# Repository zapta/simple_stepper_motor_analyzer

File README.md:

# Simple Stepper Motor Analyzer

**NOTE:** (April 2023) A new design of a stepper motor analyzer is available at 
https://github.com/zapta/ble_stepper_motor_analyzer. The new design has similar capabilities to this one but uses a Bluetooth link and a Mac/Windows/Linux app to display the data in real time. It is also less expensive to produce and can be ordered fully assembled from JLCPCB SMD service. You can embed one or more of the new analyzers in your 3D printer and connect to them remotely whever you want.

**NOTE:** (Aug 2022) A variant of the Simple Stepper Motor Analyzer can be purchased in Japan at 
https://nyarurato.booth.pm/items/4025304 . International shipping is also available.

**IMPORTANT:** We are not associated with any seller nor do we have any experience with their products
which may or may not differ from the design here. The Simple Stepper Motor Analyzer is an *as-is*
open source design for educational purposes and people may chose to use it on their own risk.

&nbsp;

&nbsp;

&nbsp;

## Demonstration

Michael from the Teaching Tech youtube channel made [a great video explaining how stepper motors work](https://youtu.be/4iII25DGIdA) and used the Simple Stepper Motor Analyzer for some of the demonstrations. 

&nbsp;

## Highlights
* Low cost and minimalist DYI hardware design.
* Standalone. Doesn't require a computer to operate.
* Analyzes the stepper motor signals in the actual system (e.g. a 3D printer).
* Galvanically isolated current sensors. Does not interfere with the operating equipment, even when its turned off.
* Easy to connect using a pair 4 wire pass through connectors.
* Intuitive user interface with color display and a capacitive touch.
* Microstepping resolution of 1% of a full step.
* Provides momentary readings, signal patterns, and statistical measurements.
* Hardware and software are open sourced with a generous license.
* Based on free tools (Kicad, platformio, LVGL) and the Raspberry Pi Pico.
* Can be easily customized (new featured, cost reduction, data link to a computer, etc).
* Powered 5VDC, 200ma via a USB-C connector.

## Overview
Diagnosing the operation of stepper motor in 3D printers and CNC machines used to require stepper motor analyzers that costs thousands of dollar. Not anymore! The Simple Stepper Analyzer ('Analyzer' in short) brings these capabilities to every maker for a tiny fraction of the price and with a minimalist DIY electronic design that leaves the heavy lifting to the firmware.

The Analyzer is self contained, has two 4-wires pass-through connectors connecting the stepper motor, is powered from a common 5V charger with a micro USB cable, provides a simple to use graphical user interface with a 3.5" color touch screen, and provides a plethora of stepper motor measurements.

The Analyzer is provided to the community as a public domain reference design that can be built and used as is, or be customized with additional features or for a lower cost as desired. The hardware and firmware come with a liberal open source license (CC0) that allows commercial usages and doesn't require code source code sharing.

---
## Disclaimer
THE DESIGN IS PROVIDED "AS IS", WITHOUT WARRANTY OF ANY KIND, EXPRESS OR IMPLIED, INCLUDING BUT NOT LIMITED TO THE WARRANTIES OF MERCHANTABILITY, FITNESS FOR A PARTICULAR PURPOSE AND NONINFRINGEMENT. IN NO EVENT SHALL THE AUTHORS OR COPYRIGHT HOLDERS BE LIABLE FOR ANY CLAIM, DAMAGES OR OTHER LIABILITY, WHETHER IN AN ACTION OF CONTRACT, TORT OR OTHERWISE, ARISING FROM, OUT OF OR IN CONNECTION WITH THE DESIGN OR THE USE OR OTHER DEALINGS IN THE DESIGN.

---
## How does it work?
The principle of operation is very simple, and so is the hardware design. The stepper motor is connected via 4 wire pass-though connectors that allow the Analyzer to monitor the current through the stepper's coils. The Analyzer's user low impedance current sensors that are galvanically isolated such does not interfere with the operation of the 3D printer or other equipment it monitors. The Analyzer measures the coils currents 100k times a second and uses firmware that analyzes the data, extracts the desired measurements, and present them on the screen. For example, this is how an analysis of the distribution of distance by speed distribution looks like:

---
## Operation is simple and intuitive

1. Turn off power to the equipment (e.g. 3D printer).
2. Disconnect the 4 wires of the stepper motor and connect them through the Analyzer two pass through connectors.
3. Power the analyzer using a 5V charger and a micro USB cable.
4. Turn on the equipment and get the stepper going.
5. Use the Analyzer's screen to view the measurements you want.

**NOTE:** The two pass-through connectors of the Analyzer are symmetric and  each can act as an input or output. 

**CAUTION:** Always connect and disconnect stepper motors when their controller is not energized, to reduce the risk of damage to the controller due to high voltage spikes. The analyser itself is not subject to that risk since its uses galvanically isolated current sensors.

**NOTE:** The only requirement for proper wiring is that the two wires of one coil should go through pins pair 1,2 and the two wires of the other coil should go through pin pair 3,4. The Analyzer doesn't care about the +/- polarity of the wires in each pair, nor does it care which of the two pass-through connectors is on the controller side and which one is on the stepper side.

**TRIVIA:**: The pin-out and the connector type of the Analyzer follows the Duet3D conventions, except that is uses right angle connector to save space.

---
## The Home Page
The Home page is first page shown when the Analyzer is powered on. It provides summary information as well as access to the Settings page.

&nbsp;

#### Page Data

Field | Description
:------------ | :-------------
 COIL&nbsp;1 | Momentary coil 1 current in Amps.
 COIL&nbsp;2 | Momentary coil 2 current in Amps.
 ERRORS | The number of phase errors detected so far. Phase errors happens when the current patterns are so distorted that a forward/backward movement cannot be determined.
 POWER | Indicates if the stepper motor is currently energized. This is determined by the sum of currents in they two coils.
 IDLES | The number of times that stepper motor change status from energized to non energized.
 STEPS | The distance the stepper moved so far. Each full step forward increments this value by one and each full step backward decrements it by one. When the stepper motor is energized, the display also shows fractional steps in resolution of 1/100th of a full step.

HINT: The fractional step value cannot be reset because it is derived from the momentary currents in the two coils. Only the stepper motor driver can reset the fraction by positioning the stepper motor on an exact full step.

HINT: To swap forward/backward directions of the Analyzer use the Settings page. This does not affect the stepper motor itself.

&nbsp;
#### Page Actions

Action | Description
:------------: | :-------------
 | Clear all data.
 | Open the Settings page.

&nbsp;

---

## The Settings Page

This is a special page that is accessible from the Home page and allows to calibrate the Analyzer. The settings are stored in a non volatile memory and are preserved when the Analyzer is turned off.

&nbsp;
#### Page Data

Data | Description
:------------: | :-------------
COIL&nbsp;1 | The momentary current of stepper coil 1 in Amp units. Should be zero, or very close to zero, when the stepper motor is disconnected.
COIL&nbsp;2 | The momentary current of stepper coil 2 in Amp units. Should be zero, or very close to zero, when the stepper motor is disconnected.

&nbsp;
#### Page Actions

Action | Description
:------------: | :-------------
SET ZERO | Used to calibrate the zero reading of the current sensors. To do so, Disconnect the stepper motor and press this button.
REVERSE STEPS DIRECTION | Changes the forward/backward step directions of the Analyzer. Does not affect the stepper motor itself. Having the correct direction is important for measurements such as the Retraction analysis.
 | Press exist the Settings page.

&nbsp;

---

## The Speed Dial Page

This page measure the stepper speed in units of full steps per second. 

&nbsp;
#### Page Data

Data | Description
:------------ | :-------------
Speed&nbsp;Dial | The speed dial shows the momentary stepper speed in full steps per second units. Forward speed is on the right side and backward speed is on the left.
Speed&nbsp;Value | This field shows the speed in a numeric form. IT is updated less frequently than the dial to allow easy reading.

&nbsp;
**HINT:** The Settings page allows to swap the forward/backward directions.

&nbsp;
#### Page Actions

Action | Description
:------------: | :-------------
 | Clears all data.
Tap the dial |Toggles the dial's speed range.

&nbsp;

---

## The Distance Graph Page

This page shows scrolling graph with the total number of full steps vs. time.

&nbsp;

#### Page Data

Data | Description
:------------ | :-------------
Distance&nbsp;Graph | This graph shows how the distance, in units of full steps, changes over time.
Distance&nbsp;value | The numeric value of the distance in full steps.  This fields is identical to the STEPS field in the Home page.

&nbsp;

#### Page Actions

Action | Description
:------------: | :-------------
 | Clears all data.
Tap the graph | Toggles the range of the vertical axis.

&nbsp;

---

#### The Retraction Graph Page

This page is useful to analyze the retraction in of 3D printer extruder.

&nbsp;
**TRIVIA:** The graph above was taken while testing a direct extruder printer with [Thing #909901](https://www.thingiverse.com/thing:909901).
&nbsp;
#### Page Data

Data | Description
:------------ | :-------------
Retraction&nbsp;Graph | This graphs tracks the retraction of 3D extruder full step units.  Retraction is defined as the filament length that was inside the extruder and is now retracted outside of the extruder. 
Retraction value |  This field shows the current retraction level in a numeric form.

&nbsp;
#### Page Actions

Action | Description
:------------: | :-------------
 | Clear all data.
Tap the graph | Changes the range of the vertical axis.

&nbsp;

---

## The Time by Speed Page

This page shows an histogram with the distributing of time by stepper speed. That is how much time was spent in each speed range. The values are normalized such that the longest bar is always at 100%.

&nbsp;
#### Page Data

Data | Description
:------------ | :-------------
Time&nbsp;Histogram | The horizontal axis indicates speed in full steps per second units. The height of each bar indicate the time of all steps in that speed range, with the length of the longest bar normalized to 100%.

&nbsp;
#### Page Actions

Action | Description
:------------: | :-------------
 | Clear all data.

&nbsp;

---

## The Distance by Speed Page

This page shows an histogram with the the distribution of distance by stepper speed.

&nbsp;
#### Page Data

Data | Description
:------------ | :-------------
Distance&nbsp;Histogram |  The horizontal axis indicates speed in full steps per second units. The height of each bar indicate the distance or number of steps in that speed range, with the length of the longest bar normalized to 100%.

&nbsp;
#### Page Actions

Action | Description
:------------: | :-------------
 | Clear all data.

&nbsp;

---

## The Current by Speed Page

This page measures the ability of the stepper motor's controller to maintain peak current at high speeds.

The screenshot below shows a healthy system where the peak current is virtually flat across the speed range.

The screenshot below shows a system that is not capable to maintain peak current and starves the stepper motor at high speeds, resulting in poor torque and possible skipped steps.

&nbsp;
#### Page Data

Data | Description
:------------ | :-------------
Peak&nbsp;Current&nbsp;Histogram | The horizontal axis indicates speed in full steps per second units. The height of each bar indicates the average peak current in Amps of  steps that speed range. 

&nbsp;
#### Page Actions

Action | Description
:------------: | :-------------
 | Clear all data.

&nbsp;

---

## Coil Current Patterns Page

This page shows the current patterns in the two stepper coils.

The screenshot below shows a healthy system where the signals are nice and clean and reaches the target peak current.

&nbsp;

The screenshot below is from a poor system where high speed results in distorted and insufficient current, resulting in loss of torque and a potential for skipped steps.

&nbsp;

**GENERAL INFORMATION:** Each cycle of the stepper current pattern represent 4 full steps. The centers of those steps are at on the four vertical dotted lines where the currents of the two coils are identical, in the same or in  opposite polarities. The transitions between the steps are on the 4 vertical solid lines where one of the coils is at zero current. This cycle of 4 full steps is sometimes referred to as a single 'electric rotation'. The analyzer computes the exact phase on this cycle using the standard trigonometric function atan2(current1, current2) which can also be calculated manually from the current readings in the Home page.

&nbsp;

#### Page Data

Data | Description
:------------ | :-------------
Current&nbsp;graph | The horizontal axis indicates time in milliseconds. The vertical axis indicate coil current level in Amps. The two graphs show the current patterns of the respective stepper coils.

**NOTE:** The graph is updated only when sufficient stepper motor movement is detected.

&nbsp;
#### Page Actions

Action | Description
:------------: | :-------------
 | Clear all data.
 | When running, pauses the display updates.
 | When paused, resume the display updates.
Tap the graph | This toggles the range of the horizontal axis.

&nbsp;

---

## Coil Current Phase Page

This page draws the current patterns of the two coils as a [Lissajous curve](https://en.wikipedia.org/wiki/Lissajous_curve) which allows to examine visually distortions such as non sinusoidal current, phase distortion, and reduced amplitude.

In an ideal system, the graph is a perfect smooth circle, that doesn't change its size when the stepper's speed changes. Patterns that significantly diverge from that indicates a sub optimal configuration and operation.

Following picture shows a pattern from a well functioning system. The graph is round, reasonable smooth, and has sufficient size which indicates good current drive. 

The horizontal axis indicates the coil 1 current and the vertical axis indicates coil 2 current. In this example, both span nicely between -2A to +2A.

&nbsp;

The screenshot below is from a poor system where high speed results in distorted and insufficient current, resulting in loss of torque and a potential for skipped steps. The pattern is far from a clean circle and the shape has reduced size.

&nbsp;

The screenshot below shows a sub optimal operation where a a speed increase of the stepper results in small (less current and torque) and even more distorted curve.

&nbsp;

The screenshot below shows a well functioning system. The smaller size of the circle compare to the example above indicates that it operates on lower current.

&nbsp;

The screenshot below show an operation of a stepper in full steps mode. The dimension of the pattern indicate good current feed, and the square  shape is the best a full step driver can deliver.

&nbsp;

The screenshot below show an operation of a stepper in half steps mode. The dimension of the pattern indicate good current feed, and the shape is somewhere between the square shape of full step mode and the round shape of micro stepping interpolation mode.

&nbsp;

#### Page Data

Data | Description
:------------ | :-------------
Lissajous&nbsp;curve | A Lissajous curve drawn from the current pattern of coil 1 (x) and coil2(y). 
Capture speed | Shows the signal capture time. Fast mode works better with fast moving steppers and slow mode works with slow moving steppers. Tap the graph to toggle.

**NOTES** 
* The graph is updated only when sufficient stepper motor movement is detected.
* To view the current pattern that resulted in the current phase pattern, use the navigation button to switch the current patters page, and vice versa.

&nbsp;
#### Page Actions

Action | Description
:------------: | :-------------
 | Clear all data.
 | When running, pauses the display updates.
 | When paused, resume the display updates.
Tap the graph | This toggles the capture time between fast and slow speeds.

&nbsp;

---

## Reference Design Specification

Item | Specification
:------------ | :------------- 
Power consumption | 5V, 175ma.
Power connector | micro USB
MCU | Raspberry Pi RP2040 (Pico module).
Flashing | Drag and drop to a virtual disk.
Data link | USB/Serial link available but not used.
Current measurement | +/-2.5A per coil. (+/-5A sensors optional).
PCB | 102mm x 57mm, two layers
Enclosure | 3D printed, 108.4mm x 63.4mm x 16.6mm
Display | 3.5" 480 x 320, Color, Landscape mode.
Touch screen | Capacitive
Sensor isolation | See ACS70331 data sheet
Sampling rate | 100Khz per channel.
Sampling resolution | 12bits
Current accuracy | estimated at +/- 1%
Max step rate | Software dependent. Currently 2K full steps/sec.
Step resolution | 1/100th of a full step.
User settings storage | On board FLASH.
GUI framework | LVGL library. R3G3B2 color depth.
Programming language | C++
Programming IDE | VSCode, Platformio, WizIO.
Electronic design software | Kicad.
Mechanical design software | Onshape. 

&nbsp;

---

## I want to build me one

The electronic schematic, PCB layout, gerber files, and the firmware source files and released binary are all available on this github repository.

[Schematic](./kicad/stepper_analyzer.pdf)

[Production files](./kicad/JLCPCB)

[BOM](./kicad/BOM.xlsx)

&nbsp;

**Instructions:** Order the PCB with JLCPB with SMD service (see JLCPCB directory with gerbers and bom and pos files). Attach the Pico with XFasten tape and solder. Cut the bottom pins of the KF2510 connectors to 1mm length and solder from the top of the PCB only. Solder the current sensors, attach the TFT to the back of the PCB with XFasten tape and carefully connect the two FPC cables. Program the Pico by connecting it to a computer while it's bootsel button is pressed and drag he uf2 release file to the virtual disk you will see on your computer.

Note: The two servo connectors may be hard to insert and remove due to a small bump on the male side that is intended to lock in place the female connector. If you are handy with X-Acto knife, you can try carefully scraping that bump for easier insertion as I did (knives are sharp and may be dangarous, use proper precautions). 

&nbsp;

&nbsp;

&nbsp;

&nbsp;

## Mechanical
3D print the two part of the enclosure (STL files in this github repository), insert the four M2.5x3.5x3 heated inserts with a solder iron, drill the four  2.5 holes in the cover, insert the PCB to the front part, make sure the TFT seats flush with front and secure the back with four M2.5x10 hex cup screws.

## Ideas for improvements
The Analyzer is provided as a fully functional reference design and changes and the developers encourage improvement/modifications of the hardware and/or firmware are encouraged. This can include new features, new measurements and pages, extending the design to support 2 or 3 steppers at once to track the x/y/z of a 3D printer, reducing the hardware cost using less expensive screen TFT, or even eliminating the screen altogether and using the Analyzer as a dongle tethered to a computer via the existing USB/Serial link.

&nbsp;

---

## FAQ

#### Q: Can I buy from you a few units?

A: We cannot provide assembled units for the general public. For that reason, we released the design with CC Zero license with the hope that other entrepreneurs will do so.

#### Q: Where do you source the TFT panels?

A: We buy the '3.5 LCD CTP' variant here https://www.aliexpress.com/item/32862869103.html. The choice of TFT panel and the mechanical design of the PCB follows Dustin Watts' ESP32 Touchdown project https://www.tindie.com/products/dustinwattsnl/esp32-touchdown/ (with extra 2mm to the PCB's length for extra clearance for the threaded heat inserts).

#### Q: Can the firmware of the analyzer be updated?

A: Yes. New firmware is released as .uf2 files. To flash the analyzer with a compatible .uf2 follow the standard procedure of the Raspberry Pi Pico. Access to the BOTSEL button is provided by a hole at the back of the 3D printed enclosure.

#### Q: Why some footprints on the PCB are not populated?

A: The PCB design includes circuitry that helps developing firmware for the analyzer that is not necessary or helpful for normal opeation of the analyzer.

#### Q: Can the current scale of the two channels increased from +/-2.5A?

A: The PCB was designed to accept also +/-5A variants of the current sensors and the optionals resistors R8 R9 were added to allow configuring the firmware to know about the larger current scale. This however was not tried yet since most 3D printer steppers do not exceed currents of 2.5A.

#### Q: Why not a SPI based TFT?

A: We could not achieve fast enough display refresh rate with SPI so switched to 16 bit parallel data transfers. With the optimized firmware we can update rate equivalent to 200Mhz SPI. 

#### Q: Can a cheaper TFT/touch be used?
A: Yes, but it will require design changes.

#### Q: Can the TFT screen be eliminated?
A: Yes. The Analyzer has a USB/Serial output can a small Analyzer dongle can communicate with a computer program. This will require firmware changes.

#### Q: Can you add feature X or customization Y?

A: Most likely not. The reference design is provided for the community to change and mix.

#### Q: I want to commercialize or crowd source it, can you help me?

A: Not really. The reference design is open source and you will need to find others to help you. We don't mind though to answer questions.

#### Q: Where do I file a bug?

A: Use the github repository.

#### Q: Is it ok to connect/disconnect power to the Analyzer while my 3D printer prints?

A: Of course. The Analyzer is isolated from the stepper wires and should not interfere with the operation of the printer.

#### Q: The Analyzer uses LVGL lib, what is the license of that library?

A: At the time of writing this, the LVGL license is available here https://github.com/lvgl/lvgl/blob/master/LICENCE.txt.  The Analyzer's developers are not affiliated with LVGL.

#### Q: Is the LVGL library included in the Analyzer's repository?

A: It's not needed. LVGL is supported by platform.io so the Analyzer's project is set for platform.io to fetch LVGL automatically.

#### Q: Can the firmware be built with the standard Raspberry Pi Pico C++ SDK?

A: It should be but we didn't try it. Installing the SDK, libraries and tools using platformio and the WizIO Pico 'baremetal' distribution is easier.

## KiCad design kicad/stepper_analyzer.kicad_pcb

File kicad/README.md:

# IMPORTANT: Do not use the latest files in this directory to build your analyzer. Instead, use the latest hardware release in this github repository. The latest files in this directory can be a work in progress toward a next stable release.

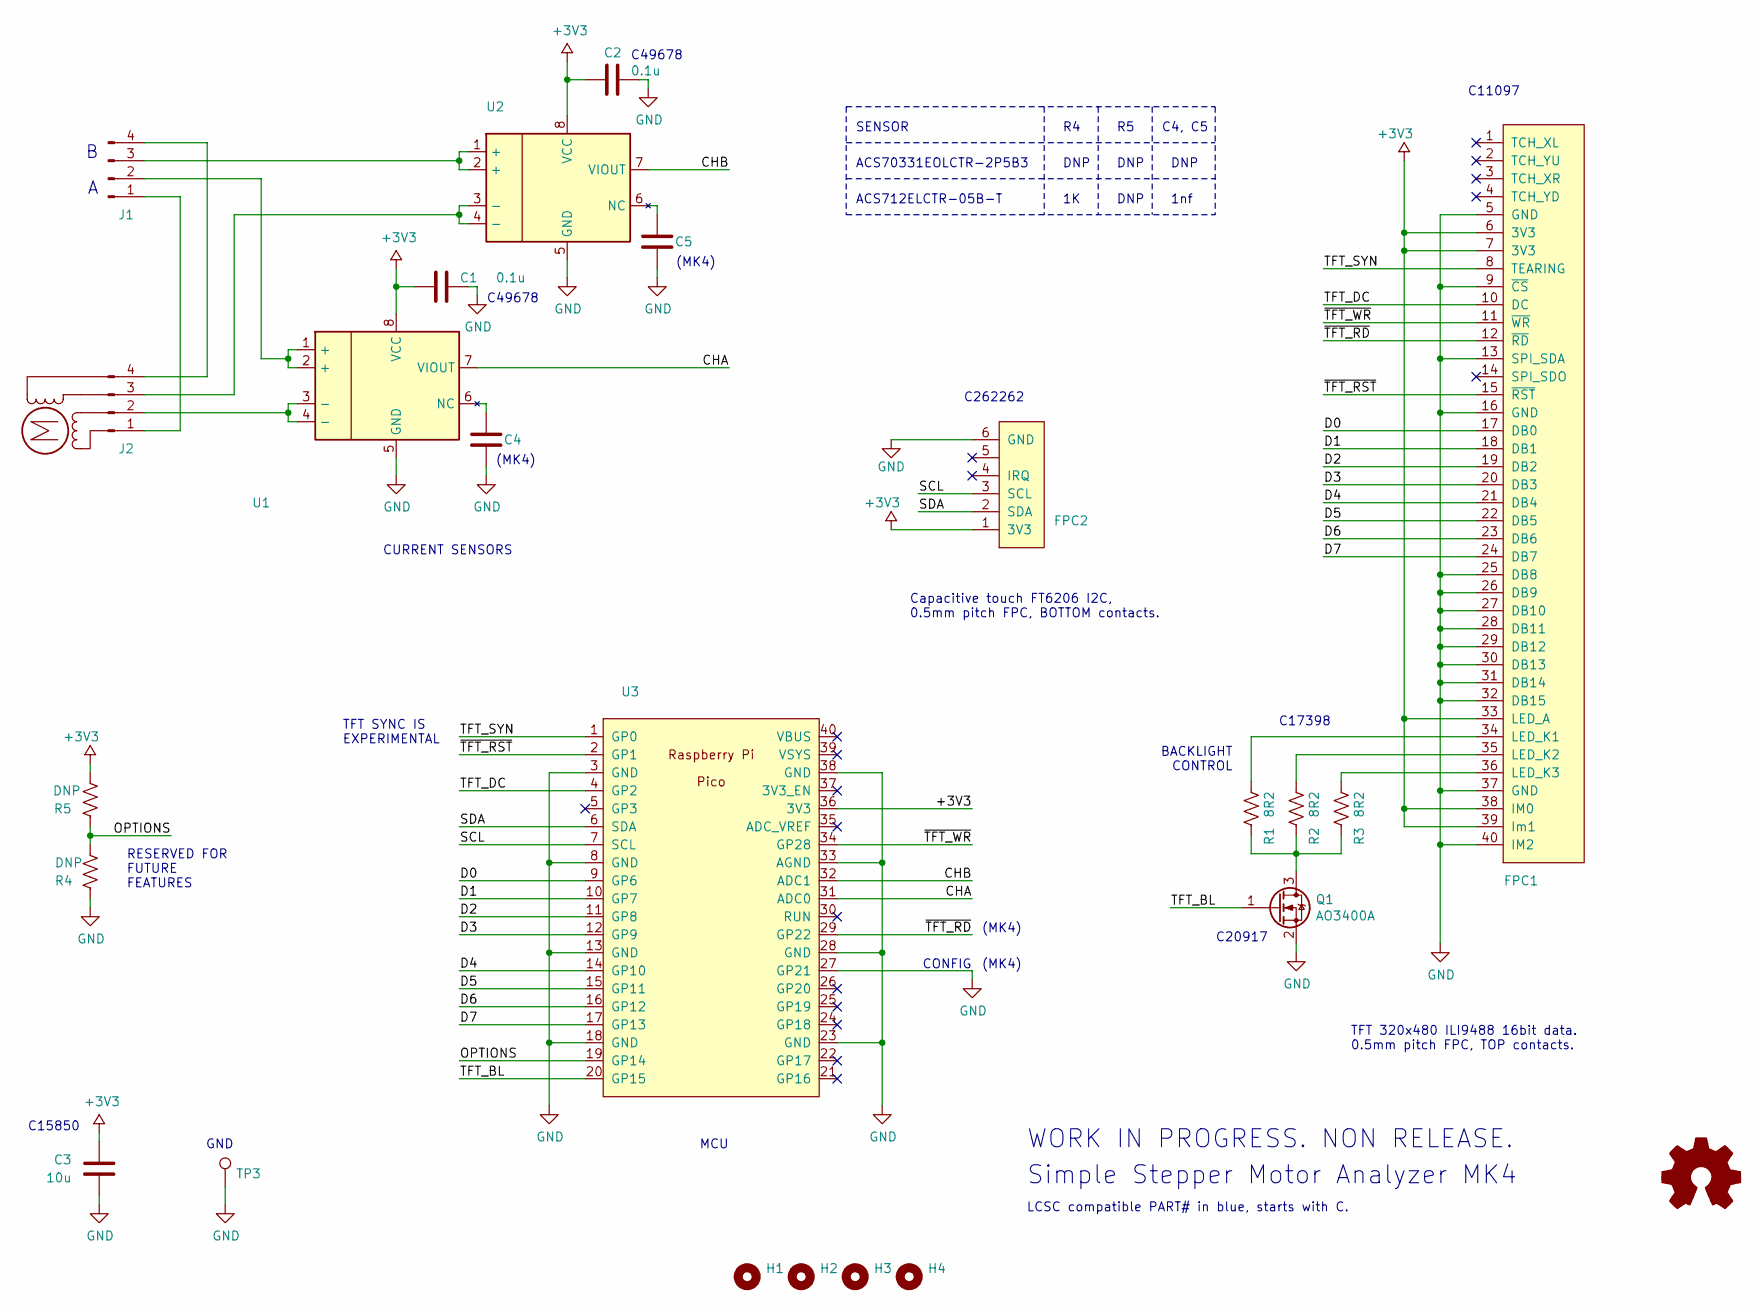
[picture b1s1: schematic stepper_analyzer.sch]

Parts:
C1, C2: 0.1u; C_0805_2012Metric_Pad1.15x1.40mm_HandSolder; LCSC C49678
C3: 10u; C_0805_2012Metric_Pad1.15x1.40mm_HandSolder; LCSC C15850
C4: 1nf; C_0805_2012Metric_Pad1.15x1.40mm_HandSolder; LCSC C49678
C5: DNP; C_0805_2012Metric_Pad1.15x1.40mm_HandSolder; LCSC C49678
FPC1: Connector_Conn_01x40_Female; JUSHUO-AFC07-S40ECC-00_40P_05mm_flipped; LCSC C11097
FPC2: FPC connector, 6 pins, 0.5mm, BOTTOM contacts; JUSHUO-AFC01-S06FCC-00_6p_05mm; LCSC C262262
H1, H2, H3, H4: MountingHole; MountingHole_2.5mm_Pad_Via
J1, J2: Connector_Conn_01x04_Male; connector_4pins_horizontal
LOGO1: Logo_Open_Hardware_Small; OSHW-Logo2_9.8x8mm_SilkScreen
M1: Motor; null_footprint
Q1: AO3400A; SOT-23; LCSC C20917
R1, R2, R3: 8R2; R_0805_2012Metric_Pad1.15x1.40mm_HandSolder; LCSC C25330
R4: DNP; R_0805_2012Metric_Pad1.15x1.40mm_HandSolder
R5: DNP; R_0805_2012Metric_Pad1.15x1.40mm_HandSolder_no_3d
TP3: TestPoint; testpoint_double_side
U1, U2: (CURRENT SENSOR); SOIC-8_3.9x4.9mm_P1.27mm
U3: Pico; Pico_smd_dedicated

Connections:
+3V3: C1.2, C2.2, C3.2, FPC1.6 (3V3), FPC1.7 (3V3), FPC1.33 (LED_A), FPC1.38 (IM0), FPC1.39 (Im1), FPC2.1 (3V3), R5.2, U1.8 (VCC), U2.8 (VCC), U3.36 (3V3)
/CHA: U1.7 (VIOUT), U3.31 (ADC0)
/CHB: U2.7 (VIOUT), U3.32 (ADC1)
/D0: FPC1.17 (DB0), U3.9 (GP6)
/D1: FPC1.18 (DB1), U3.10 (GP7)
/D2: FPC1.19 (DB2), U3.11 (GP8)
/D3: FPC1.20 (DB3), U3.12 (GP9)
/D4: FPC1.21 (DB4), U3.14 (GP10)
/D5: FPC1.22 (DB5), U3.15 (GP11)
/D6: FPC1.23 (DB6), U3.16 (GP12)
/D7: FPC1.24 (DB7), U3.17 (GP13)
/OPTIONS: R4.1, R5.1, U3.19 (GP14)
/SCL: FPC2.3 (SCL), U3.7 (SCL)
/SDA: FPC2.2 (SDA), U3.6 (SDA)
/TFT_BL: Q1.1 (G), U3.20 (GP15)
/TFT_DC: FPC1.10 (DC), U3.4 (GP2)
/TFT_SYN: FPC1.8 (TEARING), U3.1 (GP0)
/~TFT_RD: FPC1.12 (~RD), U3.29 (GP22)
/~TFT_RST: FPC1.15 (~RST), U3.2 (GP1)
/~TFT_WR: FPC1.11 (~WR), U3.34 (GP28)
GND: C1.1, C2.1, C3.1, C4.1, C5.1, FPC1.5 (GND), FPC1.9 (~CS), FPC1.13 (SPI_SDA), FPC1.16 (GND), FPC1.25 (DB8), FPC1.26 (DB9), FPC1.27 (DB10), FPC1.28 (DB11), FPC1.29 (DB12), FPC1.30 (DB13), FPC1.31 (DB14), FPC1.32 (DB15), FPC1.37 (GND), FPC1.40 (IM2), FPC2.6 (GND), Q1.2 (S), R4.2, TP3.1, U1.5 (GND), U2.5 (GND), U3.3 (GND), U3.8 (GND), U3.13 (GND), U3.18 (GND), U3.23 (GND), U3.27 (GP21), U3.28 (GND), U3.33 (AGND), U3.38 (GND)
unnamed: C4.2, U1.6 (NC)
unnamed: C5.2, U2.6 (NC)
unnamed: FPC1.34 (LED_K1), R1.2
unnamed: FPC1.35 (LED_K2), R2.2
unnamed: FPC1.36 (LED_K3), R3.2
unnamed: J1.1, J2.1
unnamed: J1.2, U1.1 (+), U1.2 (+)
unnamed: J1.3, U2.1 (+), U2.2 (+)
unnamed: J1.4, J2.4
unnamed: J2.2, U1.3 (-), U1.4 (-)
unnamed: J2.3, U2.3 (-), U2.4 (-)
unnamed: Q1.3 (D), R1.1, R2.1, R3.1

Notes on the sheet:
CURRENT SENSORS
Simple Stepper Motor Analyzer MK4
BACKLIGHT CONTROL
TFT 320x480 ILI9488 16bit data. 0.5mm pitch FPC, TOP contacts.
Capacitive touch FT6206 I2C, 0.5mm pitch FPC, BOTTOM contacts.
GND
C11097
C262262
LCSC compatible PART# in blue, starts with C.
C49678
C17398
RESERVED FOR FUTURE FEATURES
C20917
C15850
(MK4)
WORK IN PROGRESS. NON RELEASE.
CONFIG
TFT SYNC IS EXPERIMENTAL
MCU
SENSOR
ACS70331EOLCTR-2P5B3
DNP
ACS712ELCTR-05B-T
C4, C5
1nf

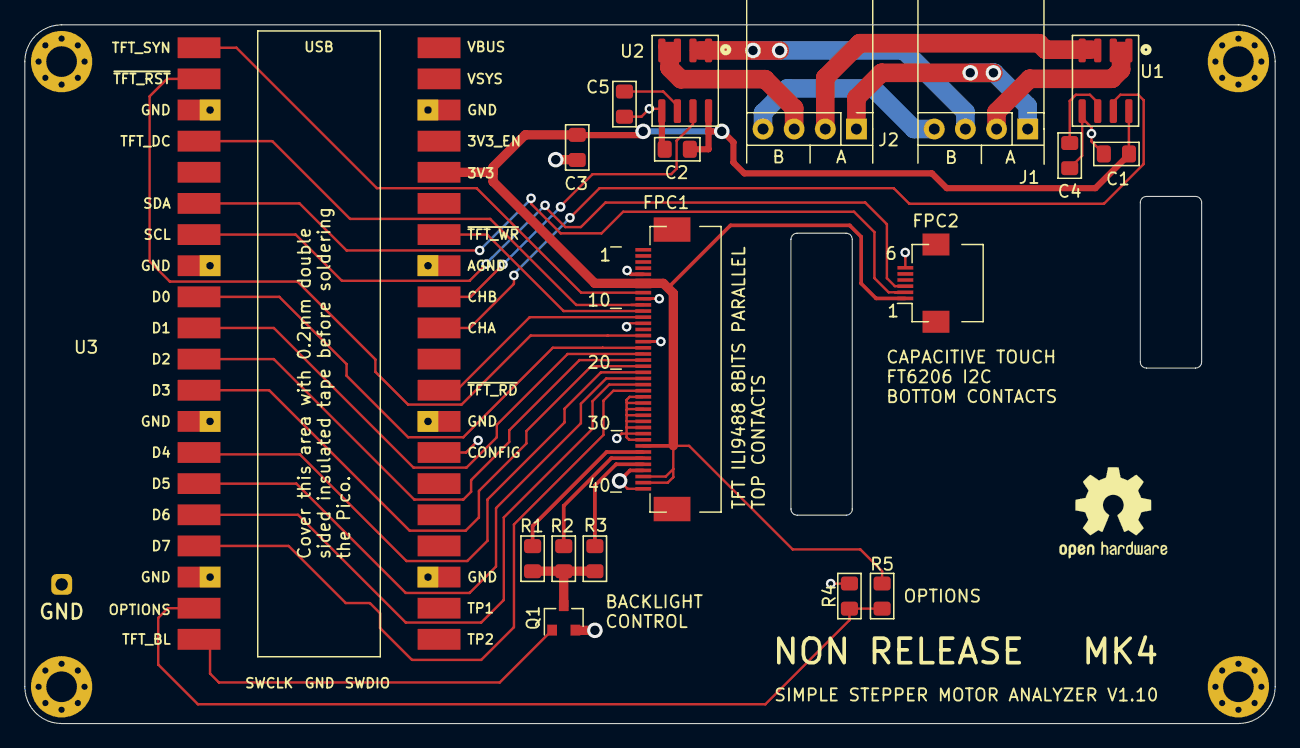
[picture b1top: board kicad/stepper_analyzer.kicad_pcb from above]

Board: 2 copper layers, 102.0 x 57.0 mm, 25 parts (1 on the bottom side), 33 nets.

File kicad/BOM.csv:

Ref,Quantity,Value,Footprint,JLCPCB Service,Comments
"C1, C2, ",2,Ceramic capacitor 100nf,SMD 0805,Yes,
"C3, ",1,Ceramic capacitor 10uf,SMD 0805,Yes,
"FPC1, ",1,"FPC connector 40 pins, 0.5mm pitch TOP contacts.",,Yes,LCSC C11097 or similar.
"FPC2, ",1,"FPC connector 6 pins, 0.5mm pitch BOTTOM contacts.",,Yes,LCSC C262262 or similar
"Q1, ",1,N-Chan MOSFET AO3400A ,SOT-23,Yes,
"R1, R2, R3, ",3,Resistor 8.2 Ohms,SMD 0805,Yes,
PCB,1,Custom PCB per gerber files,,Yes,
,,,,,
"J1, J2, ",2,"Right angle connector, 4 pins, 0.1 pitch. KF2510 ",,No,"AliExpress. Trim pins using the 3D printed jig, BEFORE soldering them."
"U1, U2, ",2,ACS70331EOLCTR-2P5B3,SOIC-8,No,AliExpress
"U3, ",1,Raspberry Pi Pico,,No,
TFT,1,"TFT module 3.5 320x480, IL9488, capacitive touch FT6206",,No,"AliExpress JR E-Shop, 3.5 LCD CTP"
Threaded heat Inserts,4,M2.5 x 3.5mm OD x 3mm length,,No,AliExpress Centrode Store
Screws,4,"M2.5 x 10mm,  hex cup head.",,No,AliExpress
Enclosure,1,Use provided 3D model,,No,
Tape,,"Double sided thermal tape 10mm width, 0.2mm thickness",,,AliExpress

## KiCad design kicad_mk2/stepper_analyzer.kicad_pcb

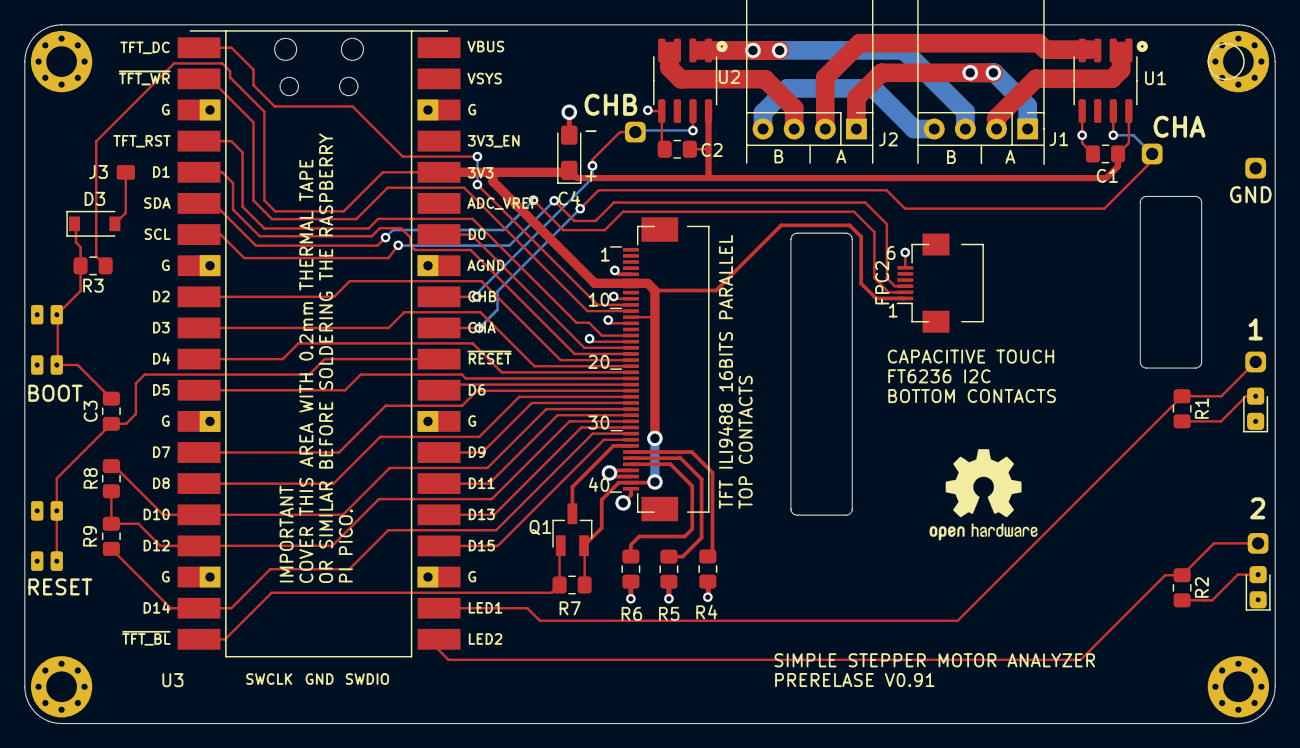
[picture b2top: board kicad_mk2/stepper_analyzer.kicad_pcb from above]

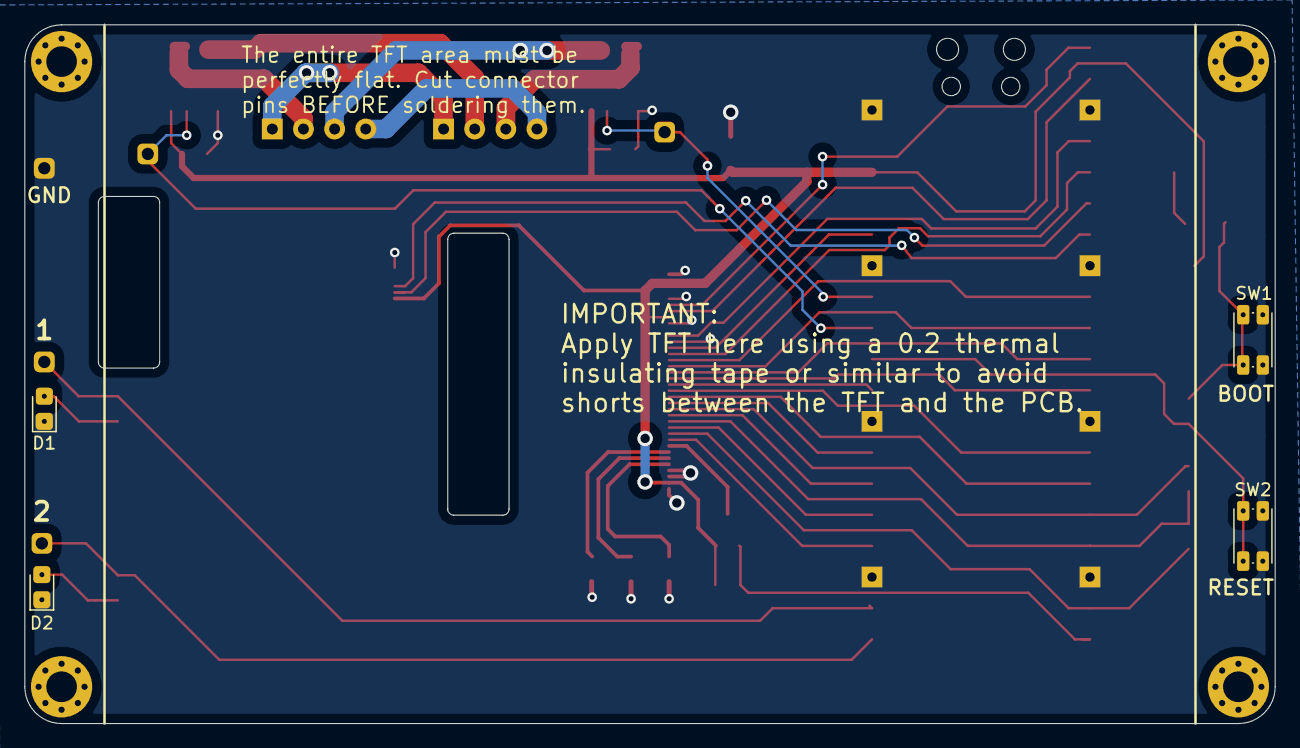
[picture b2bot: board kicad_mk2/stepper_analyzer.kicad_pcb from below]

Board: 2 copper layers, 102.0 x 57.0 mm, 38 parts (5 on the bottom side), 43 nets.

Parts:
C1, C2: 0.1u; C_0805_2012Metric_Pad1.15x1.40mm_HandSolder
C3: 0.1u; C_0805_2012Metric_Pad1.15x1.40mm_HandSolder_no_3d
C4: 10u; CP_EIA-3216-18_Kemet-A_Pad1.58x1.35mm_HandSolder
D1, D2: LED; LED_0805_2012Metric_Pad1.15x1.40mm_HandSolder_double_side_n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
D3: BAT43W; D_SOD-123_no_3d
FPC1: Connector_Conn_01x40_Female; JUSHUO-AFC07-S40ECC-00_40P_05mm_flipped
FPC2: FPC connector, 6 pins, 0.5mm, BOTTOM contacts; JUSHUO-AFC01-S06FCC-00_6p_05mm
H1, H2, H3, H4: MountingHole; MountingHole_2.5mm_Pad_Via
J1, J2: Connector_Conn_01x04_Male; connector_4pins_horizontal
J3: Conn_01x01; SolderWire-0.1sqmm_1x01_D0.4mm_OD1mm
LOGO1: Logo_Open_Hardware_Small; OSHW-Logo2_9.8x8mm_SilkScreen
M1: Motor; null_footprint
Q1: SI2301; SOT-23_hand_soldering
R1, R2: 3K3; R_0805_2012Metric_Pad1.15x1.40mm_HandSolder_no_3d
R3: 1K; R_0805_2012Metric_Pad1.15x1.40mm_HandSolder_no_3d
R4, R5, R6: 8R2; R_0805_2012Metric_Pad1.15x1.40mm_HandSolder
R7: 3K3; R_0805_2012Metric_Pad1.15x1.40mm_HandSolder
R8, R9: DNP; R_0805_2012Metric_Pad1.15x1.40mm_HandSolder_no_3d
SW1, SW2: switch; SW_Push_1P1T_NO_CK_KMR2_double_size_no_3d
TP1, TP2: TestPoint; testpoint_one_side
TP3: TestPoint; testpoint_double_side
TPL1, TPL2: TestPoint; testpoint_double_side
U1, U2: ACS70331EOLCTR-2P5B3; SOIC-8_3.9x4.9mm_P1.27mm
U3: Pico; Pico_smd_dedicated

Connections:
+3V3: C1.2, C2.2, C4.1, FPC1.6, FPC1.7, FPC1.12, FPC1.39, FPC2.1, Q1.2, R3.1, R7.2, U1.8, U2.8, U3.36
/CHA: TP1.1, U1.7, U3.31
/CHB: TP2.1, U2.7, U3.32
/D0: FPC1.17, U3.34
/D1: FPC1.18, U3.5
/D2: FPC1.19, U3.9
/D3: FPC1.20, U3.10
/D4: FPC1.21, U3.11
/D5: FPC1.22, U3.12
/D6: FPC1.23, U3.29
/D7: FPC1.24, U3.14
/D8: FPC1.25, U3.15
/D9: FPC1.26, U3.27
/D10: FPC1.27, R8.2, U3.16
/D11: FPC1.28, U3.26
/D12: FPC1.29, R8.1, R9.1, U3.17
/D13: FPC1.30, U3.25
/D14: FPC1.31, R9.2, U3.19
/D15: FPC1.32, U3.24
/LED1: R1.1, TPL1.1, U3.22
/LED2: R2.1, TPL2.1, U3.21
/SCL: FPC2.3, U3.7
/SDA: FPC2.2, U3.6
/TFT_DC: FPC1.10, U3.1
/TFT_RST: FPC1.15, U3.4
/~RESET: C3.1, SW2.2, U3.30
/~TFT_BL: Q1.1, R7.1, U3.20
/~TFT_WR: FPC1.11, U3.2
GND: C1.1, C2.1, C4.2, D1.1, D2.1, FPC1.5, FPC1.9, FPC1.13, FPC1.16, FPC1.37, FPC1.38, FPC1.40, FPC2.6, R4.1, R5.1, R6.1, SW1.1, SW2.1, TP3.1, U1.5, U2.5, U3.3, U3.8, U3.13, U3.18, U3.23, U3.28, U3.33, U3.38
unnamed: C3.2, D3.1, R3.2, SW1.2
unnamed: D1.2, R1.2
unnamed: D2.2, R2.2
unnamed: D3.2, J3.1
unnamed: FPC1.33, Q1.3
unnamed: FPC1.34, R4.2
unnamed: FPC1.35, R5.2
unnamed: FPC1.36, R6.2
unnamed: J1.1, J2.1
unnamed: J1.2, U1.1, U1.2
unnamed: J1.3, U2.1, U2.2
unnamed: J1.4, J2.4
unnamed: J2.2, U1.3, U1.4
unnamed: J2.3, U2.3, U2.4

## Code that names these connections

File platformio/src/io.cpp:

#include "io.h"

#include "hardware/gpio.h"

namespace io {

void setup() {
  // A mask with all gpio output pins we use.
  constexpr uint kOutputMask =
      1ul << LED0_PIN | 1ul << LED1_PIN | 1ul << LED2_PIN ;
      // | 1ul << TFT_D0_PIN |
      // 1ul << TFT_D1_PIN | 1ul << TFT_D2_PIN | 1ul << TFT_D3_PIN |
      // 1ul << TFT_D4_PIN | 1ul << TFT_D5_PIN | 1ul << TFT_D6_PIN |
      // 1ul << TFT_D7_PIN | 1ul << TFT_D8_PIN | 1ul << TFT_D9_PIN |
      // 1ul << TFT_D10_PIN | 1ul << TFT_D11_PIN | 1ul << TFT_D12_PIN |
      // 1ul << TFT_D13_PIN | 1ul << TFT_D14_PIN | 1ul << TFT_D15_PIN |
      // 1ul << TFT_RST_PIN | 1ul << TFT_WR_PIN | 1ul << TFT_DC_PIN |
      // 1ul << TFT_BL_PIN;


  gpio_init_mask(kOutputMask);
  
  // Start with backlight non active. Before we set it as a direction,
  // an external pullup resistor makes sure  it's high.
  //TFT_BL_HIGH;

  gpio_set_dir_out_masked(kOutputMask);
}

 }  // namespace io

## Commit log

2021-06-01 Initial set of files.
2021-06-01 Added baseline of documentation. Need to be updated for the new design.
2021-06-01 Updating documentation
2021-06-01 Updated documentation
2021-06-01 Switched the documentation
2021-06-01 Added 3D model
2021-06-01 Added a note.
2021-06-01 Renamed coil 1,2 to A,B
2021-06-02 Fixed typos and added a skeleton lib directory.
2021-06-02 Incremented version counter post release 1.0,0
2021-06-07 Cleaned up the schematic. No semantic change.
2021-06-07 Flushing changes.
2021-06-08 Refactored the tft driver to a class instance.
2021-06-09 Added a skeleton MK3 driver.
2021-06-09 Added TFT driver for MK3
2021-06-10 Updated kicad files for MK3
2021-06-10 Generated gerbers
2021-06-10 Remove orhpan text message.
2021-06-10 Regenerated gerbers.
2021-06-10 Updated label on the PCB.
2021-06-10 Updated schematic PDF.
2021-06-10 Regenerated gerbers
2021-06-10 Updated top silk text.
2021-06-10 Added missing FPC1 top silk reference.
2021-06-10 Remove A,B test points. Reduce bottom layer traces.
2021-06-10 Updated schematic.
2021-06-10 Minor schematic tweaks.
2021-06-10 Deleted backup files.
2021-06-10 Added rescue files to gitignore
2021-06-10 Added fp-info-cache to gitignore
2021-06-10 Added stepper_analyzer-cache.lib to gitignore.
2021-06-10 Added stepper_motor_analyzer.bck to gitignore.
2021-06-10 Regenerated step file.
2021-06-10 Deleted stepper_analyzer.xml
2021-06-11 Added to Settings screen display of hardware version.
2021-06-11 Renamed kicad directory to kicad_mk3
2021-06-12 Added kicad files of mk2 (old hardware version). Taken from commit d4c36661691f7af347b63aa49380aba189a09ed7
2021-06-12 Updated README.
2021-06-12 Updated pin numbers.
2021-06-12 Incremented version to 1.11
2021-06-12 Tweaked TFT insulation.
2021-06-12 Cleaned up the +3.3V path.
2021-06-12 Updated pos file.
2021-06-12 Upgraded to LVLG 7.11.0 (latest 7.x).
2021-06-12 Restored sparse grid lines. (Not upgrading to LVGL 8 for now).
2021-06-12 Replaced on-demand LVGL lib with a checked in snapshot (7.11.0)
2021-06-12 Added a comment in the LICENSE file regarding third party libraries.
2021-06-12 Updated the LICENSE doc to reflect that it covers also source files for hardware and 3D designs.
2021-06-12 Added JLCB gerbers
2021-06-12 Changed 10u from tant to ceramic.
2021-06-12 Change config jumpers to resistors.
2021-06-12 Deleted kicad_mk2, renamed kicad_mk3 to kicad.
2021-06-12 Deleted mk2_tft_driver, renamed mk3_tft_driver to tft_driver.
2021-06-12 Set version to 1.0.0
2021-06-12 Fixed silkscreen on back side.
2021-06-12 Fixed a typo.
2021-06-12 Tweaked silk screen.
2021-06-12 Renamed Config to Options
2021-06-13 Updfated Kicad TODOs.
2021-06-13 Reduced time to first screen from 1400ms to 650ms.
2021-06-13 Simplified LVGL logging.
2021-06-13 Renamed hardware-config to hardware-options.
2021-06-13 Cleaned up platformio.ini
2021-06-13 Added print of the Pico SDK version.
2021-06-14 Added verification of SDK version.
2021-06-14 Specified an exact Wizio version.
2021-06-14 Updated TODOs
2021-06-15 Added a TODO
2021-06-16 Removed the assertion about the SDK version. We now force the version in platformio.ini.
2021-06-16 Fixed link to legacy version.
2021-06-16 Fixed a broken BOM link.
2021-06-17 Added BOM file.
2021-06-17 Minor documentation change.
2021-06-18 Patched LVGL 7.11.0 to support chart minor division lines and added them in two screens.
2021-06-18 Added instructions for installing PIL.
2021-06-18 Added a TODO.
2021-06-18 Both ADC DMA channels now use IRQ0. Freed IRQ1 for future display update.
2021-06-19 Changed color depth from 8 to 16 bits.
2021-06-19 Changed the tft driver to use DMA and double buffer (speedup).
2021-06-19 Minor cleanup. Eliminated 'extern' in two files.
2021-06-19 Adapted screen capture to 16 bits colors.
2021-06-19 Improved the screenshot button.
2021-06-19 Minor tweaks.
2021-06-19 Tweaked charts major division line color.
2021-06-19 Renamed kCaptureBufferSize to kAdcCaptureBufferSize
2021-06-19 Missing rename from previous commit.
2021-06-19 More renaming.
2021-06-19 Changed the steps screen to user hard timing for the samplings rather than relying on frame rate.
2021-06-19 More files from the previous commit.
2021-06-19 Changed the retraction screen to use hard timing rather than relying on frame rate.
2021-06-19 Enabled vertical sync output (tearing effect).
2021-06-20 Changed the speed gauge screen to use hard timing rather than relying on frame rate.
2021-06-20 Incremented version to 1.0.2
2021-06-20 Clenaed up done TODOs.
2021-06-20 Added PWM control of TFT backlight. Still not exposed to the user.
2021-06-21 Updated Kicad TODOs.
2021-06-24 Updated 3D model and kicad TODOs.
2021-06-24 Updated kicad todo
2021-06-24 Added backlight intensity settings.
2021-06-24 Updated the Settings meddage.
2021-06-26 Added a Kicad TODO
2021-06-26 Added a test screen to experiment with tearring effect.
2021-06-26 Added experimental tearring code. (commented out)
2021-06-26 Minor tweaks to the TFT's PIO. Now forcing output direction as preperation to TFT reading.
2021-06-26 Incremented firmware version to 1.0.3
2021-07-01 Extended the PIO program to support TFT reads. Not supported on MK3 and eariler versions.
2021-07-02 TFT reading in single byte mode works.
2021-07-02 Added test code to read and dump the ILI9488 screen.
2021-07-02 Changed the firmware to have the RD pin at 22 (was 18).
2021-07-03 Added support for current sensor configuration. Will allow to support different sensors.
2021-07-03 Made schematic and PCB changes toward MK3. Not ready.
2021-07-03 Teaked board design toward MK4.
2021-07-04 Split between the x and y axis configurations. Will allow to support dynmic sensor selection.
2021-07-04 Added a kicad TODO.
2021-07-04 Added per sensor type range selection.
2021-07-04 Added a warning regarding using official releases of kicad files.
2021-07-04 Updated kicad note
2021-07-04 Updated screen capture to direct TFT read. Requires hardware level MK4. Does not work on MK3.
2021-07-04 Tweaked the screenshot converter.
2021-07-04 Updated Kicad TODO.
2021-07-04 Simplified screenshot converter.
2021-07-05 Added an enclosure version that doesn't need metal threaded heat inserts. Easier to source and build.
2021-07-05 Assorted tweaks.
2021-07-12 Made the shcematic non-release warning more visible.
2021-07-19 Updated enclosure 3D models to the latest in OnShape.
2021-07-26 Resoted Kicad files to V1.00 release.
2021-09-04 Added a 200 steps scale to the steps chart screen.
2021-09-04 Temp release candidate
2021-10-09 Set filtering of the second channel to 700 as well (was a typo) and removed the detection of the HAUL 5A which is not in use, reserving it to a future sensor.
2021-10-27 Added missing BOM file (deleted unintentionally in a previous commit)
2022-08-14 Added mentioning of a seller.
2022-08-14 Updated the sellers note.
2022-08-14 Added clarification that seller's product may differ from the design here.
2022-08-14 tweaked text style.
2022-08-14 Removed the self link in the README page.
2023-04-12 Updated README.md with a note about the new BLE analyzer.
